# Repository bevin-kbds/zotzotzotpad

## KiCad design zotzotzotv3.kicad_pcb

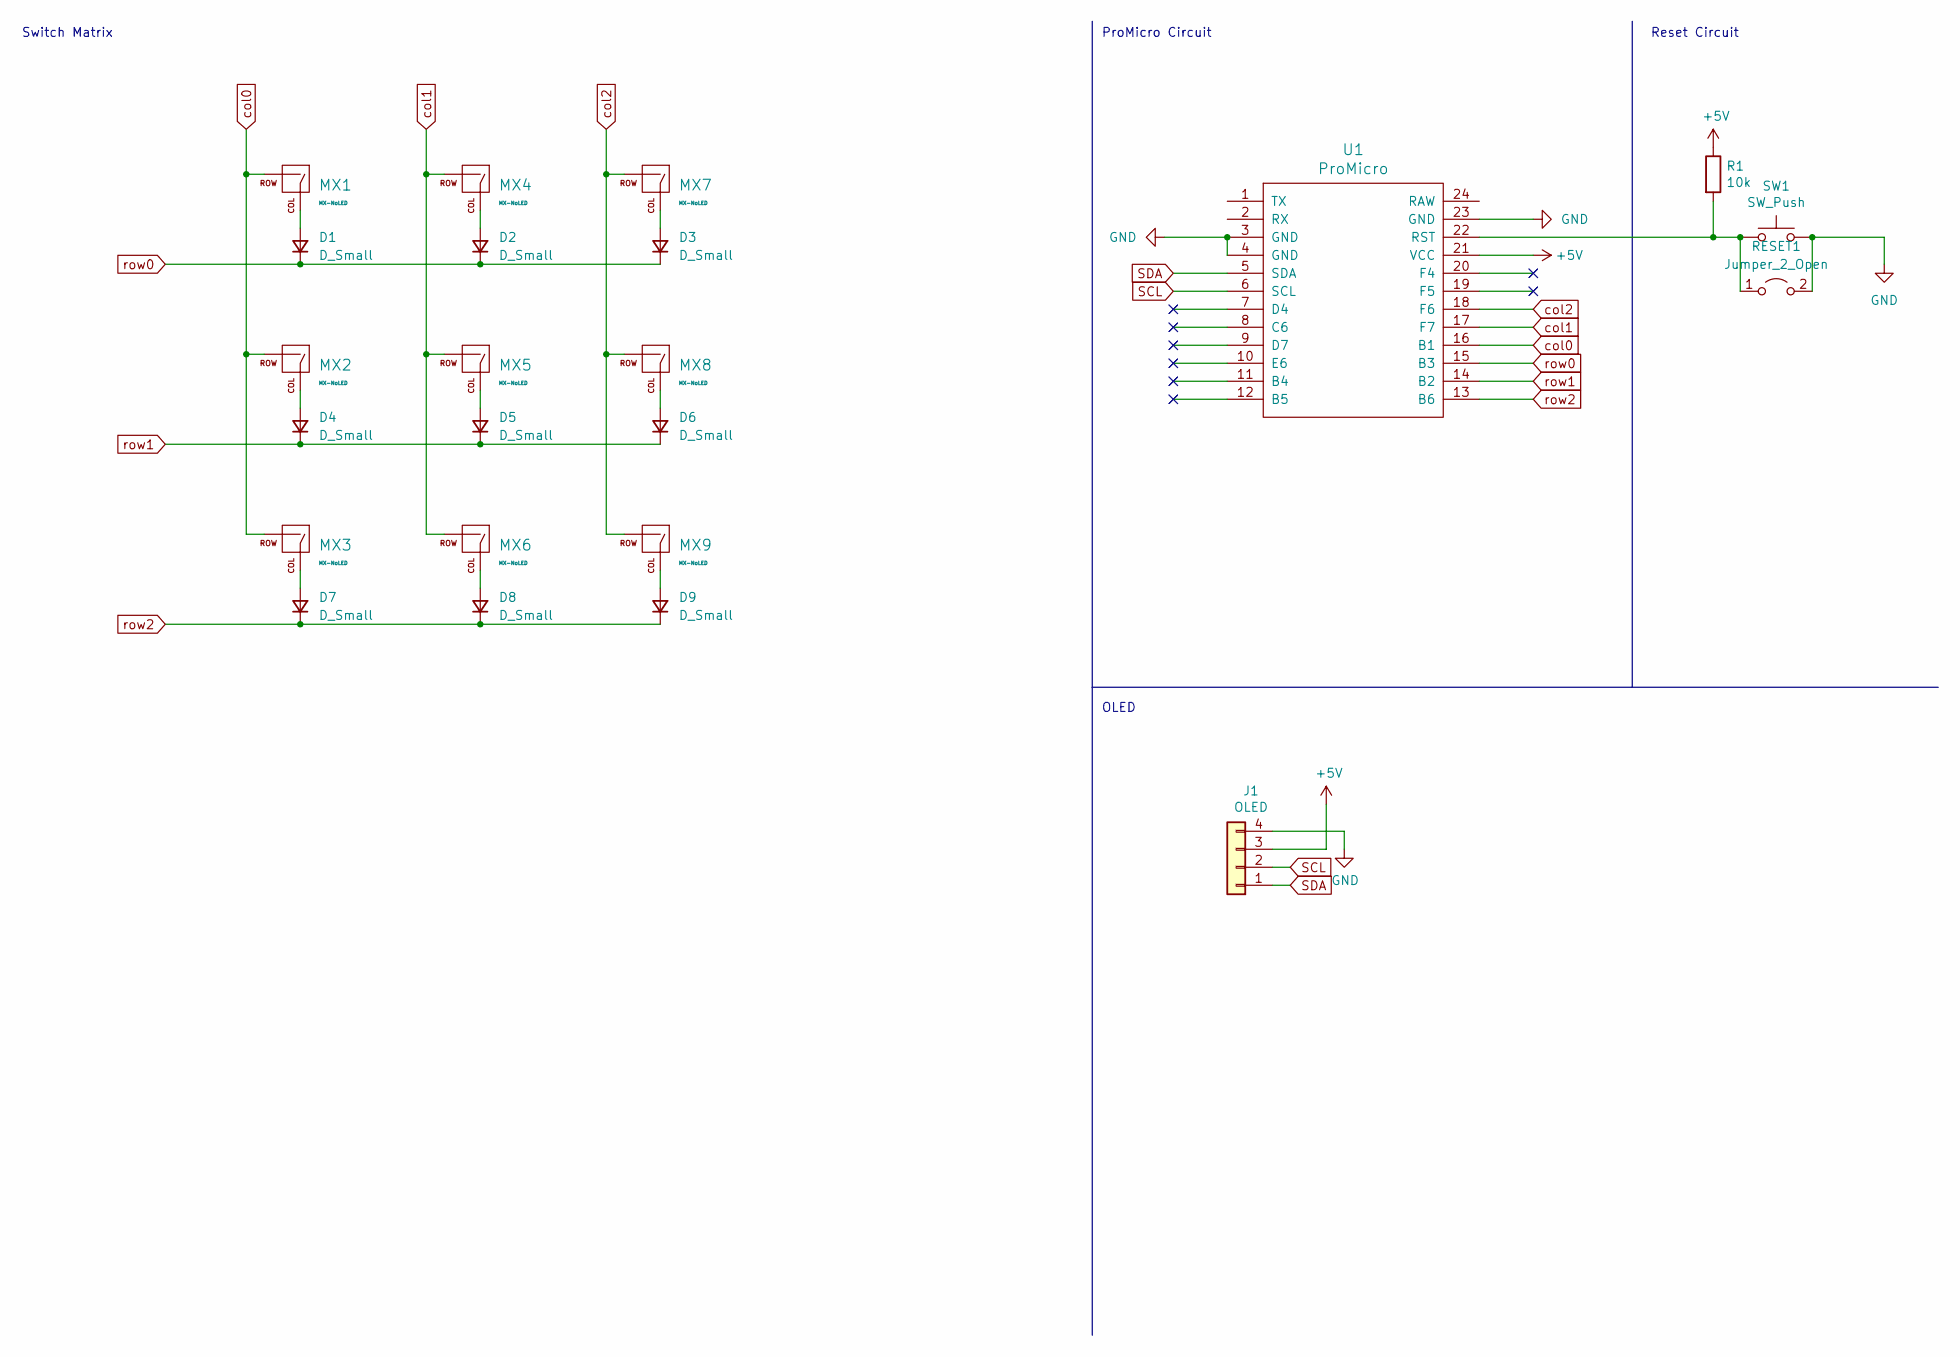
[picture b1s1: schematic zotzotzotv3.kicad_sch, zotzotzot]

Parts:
D1, D2, D3, D4, D5, D6, D7, D8, D9: D_Small; D3_TH_nonHybrid
J1: OLED; OLED_v2
MX1, MX2, MX3, MX4, MX5, MX6, MX7, MX8, MX9: MX-NoLED; MXOnly-1U-NoLED
R1: 10k; R3_TH_nonHybrid
RESET1: Jumper_2_Open; TestPoint_2Pads_Pitch5.08mm_Drill1.3mm
SW1: SW_Push; SW_SPST_TL3342
U1: ProMicro; ProMicro_v3

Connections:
+5V: J1.3, R1.1, U1.21 (VCC)
GND: J1.4, RESET1.2 (B), SW1.2, U1.3 (GND), U1.4 (GND), U1.23 (GND); also elsewhere on the board
unnamed: D1.2 (A), MX1.1 (COL)
unnamed: D2.2 (A), MX4.1 (COL)
unnamed: D3.2 (A), MX7.1 (COL)
unnamed: D4.2 (A), MX2.1 (COL)
unnamed: D5.2 (A), MX5.1 (COL)
unnamed: D6.2 (A), MX8.1 (COL)
unnamed: D7.2 (A), MX3.1 (COL)
unnamed: D8.2 (A), MX6.1 (COL)
unnamed: D9.2 (A), MX9.1 (COL)
unnamed 11: R1.2, RESET1.1 (A), SW1.1, U1.22 (RST); also elsewhere on the board
SCL: J1.2, U1.6 (SCL)
SDA: J1.1, U1.5 (SDA)
col0: MX1.2 (ROW), MX2.2 (ROW), MX3.2 (ROW), U1.16 (B1)
col1: MX4.2 (ROW), MX5.2 (ROW), MX6.2 (ROW), U1.17 (F7)
col2: MX7.2 (ROW), MX8.2 (ROW), MX9.2 (ROW), U1.18 (F6)
row0: D1.1 (K), D2.1 (K), D3.1 (K), U1.15 (B3)
row1: D4.1 (K), D5.1 (K), D6.1 (K), U1.14 (B2)
row2: D7.1 (K), D8.1 (K), D9.1 (K), U1.13 (B6)

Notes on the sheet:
Reset Circuit
ProMicro Circuit
OLED
Switch Matrix

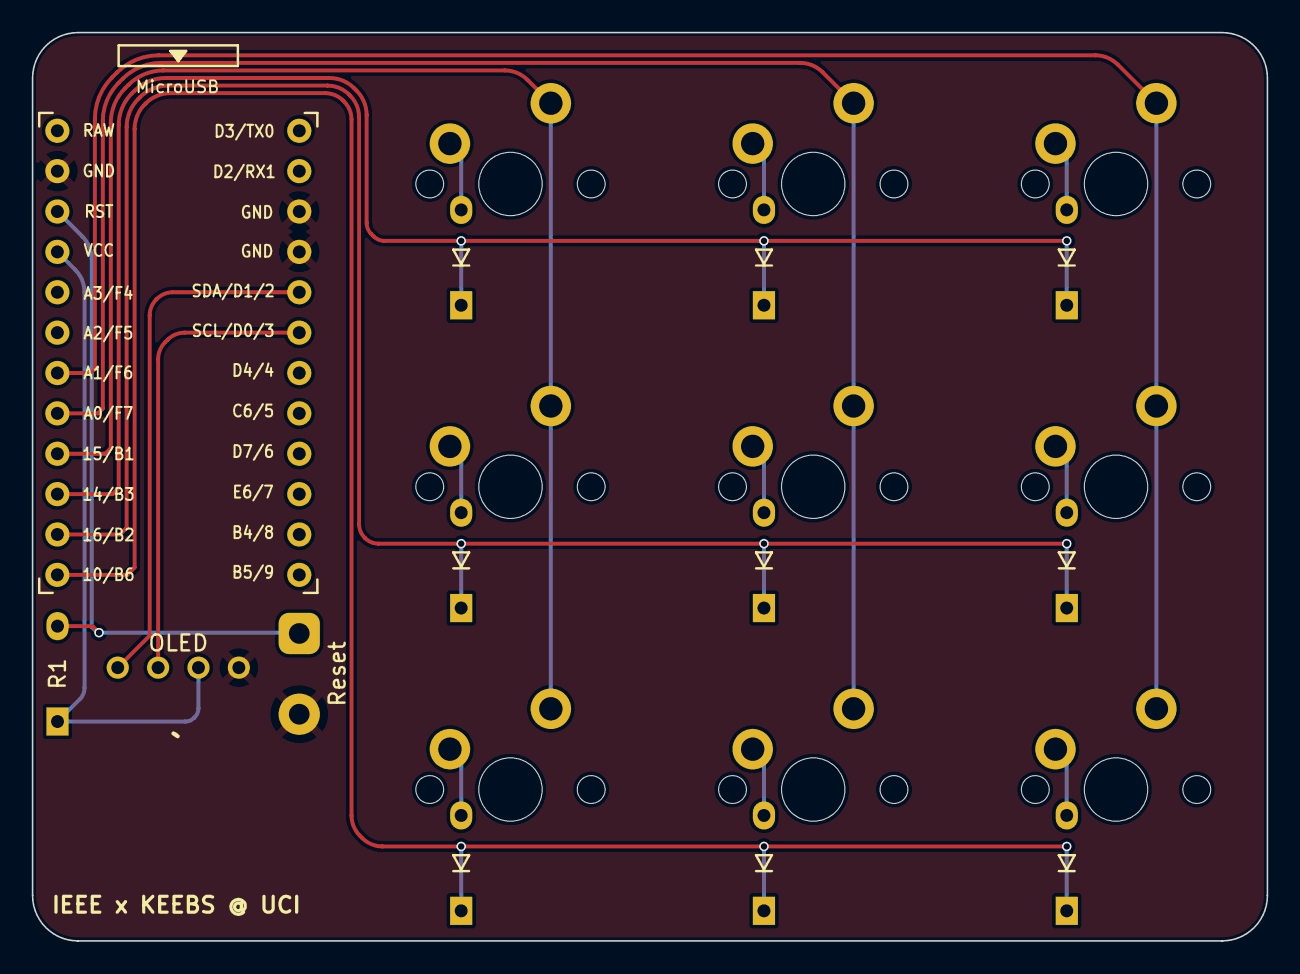
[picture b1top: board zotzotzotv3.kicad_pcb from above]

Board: 2 copper layers, 77.7 x 57.1 mm, 23 parts (1 on the bottom side), 20 nets.

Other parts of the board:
Reset: Jumper_2_Open; TestPoint_2Pads_Pitch5.08mm_Drill1.3mm

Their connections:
GND: Reset.2 (B); also elsewhere on the board
unnamed 11: Reset.1 (A); also elsewhere on the board

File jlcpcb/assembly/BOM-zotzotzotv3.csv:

Comment,Designator,Footprint,LCSC
ProMicro,U1,ProMicro_v3,
MX-NoLED,MX2,MXOnly-1U-NoLED,
MX-NoLED,MX4,MXOnly-1U-NoLED,
MX-NoLED,MX5,MXOnly-1U-NoLED,
MX-NoLED,MX3,MXOnly-1U-NoLED,
MX-NoLED,MX7,MXOnly-1U-NoLED,
MX-NoLED,MX1,MXOnly-1U-NoLED,
MX-NoLED,MX6,MXOnly-1U-NoLED,
MX-NoLED,MX8,MXOnly-1U-NoLED,
MX-NoLED,MX9,MXOnly-1U-NoLED,
OLED,J1,OLED_v2,
SW_Push,SW1,SW_SPST_TL3342,
D_Small,D5,D3_TH_nonHybrid,
D_Small,D7,D3_TH_nonHybrid,
D_Small,D4,D3_TH_nonHybrid,
10k,R1,R3_TH_nonHybrid,
D_Small,D9,D3_TH_nonHybrid,
D_Small,D1,D3_TH_nonHybrid,
D_Small,D6,D3_TH_nonHybrid,
D_Small,D2,D3_TH_nonHybrid,
D_Small,D8,D3_TH_nonHybrid,
D_Small,D3,D3_TH_nonHybrid,

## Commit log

2022-09-28 init
2022-09-28 add submodule
2022-09-28 relocated symbols and footprints
2023-03-28 THT update
2023-03-28 gerber
2023-03-28 new graphic
2023-04-03 annotated
